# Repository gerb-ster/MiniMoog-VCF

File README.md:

# YUSynth MiniMoog VCF

No system is complete without some good VCF’s. And one excellent source for some good VCF is designs is, offcourse, the website of Yven Usson, also known as YuSynth. And this VCF is no exception. It’s a clone of the famous VCF found in the MiniMoog. I’ve made an eurorack version.

## Status: Finished

- done: first schematic & board design
- done: breadboard and test
- done: design frontpanel
- done: order PCB and build prototype

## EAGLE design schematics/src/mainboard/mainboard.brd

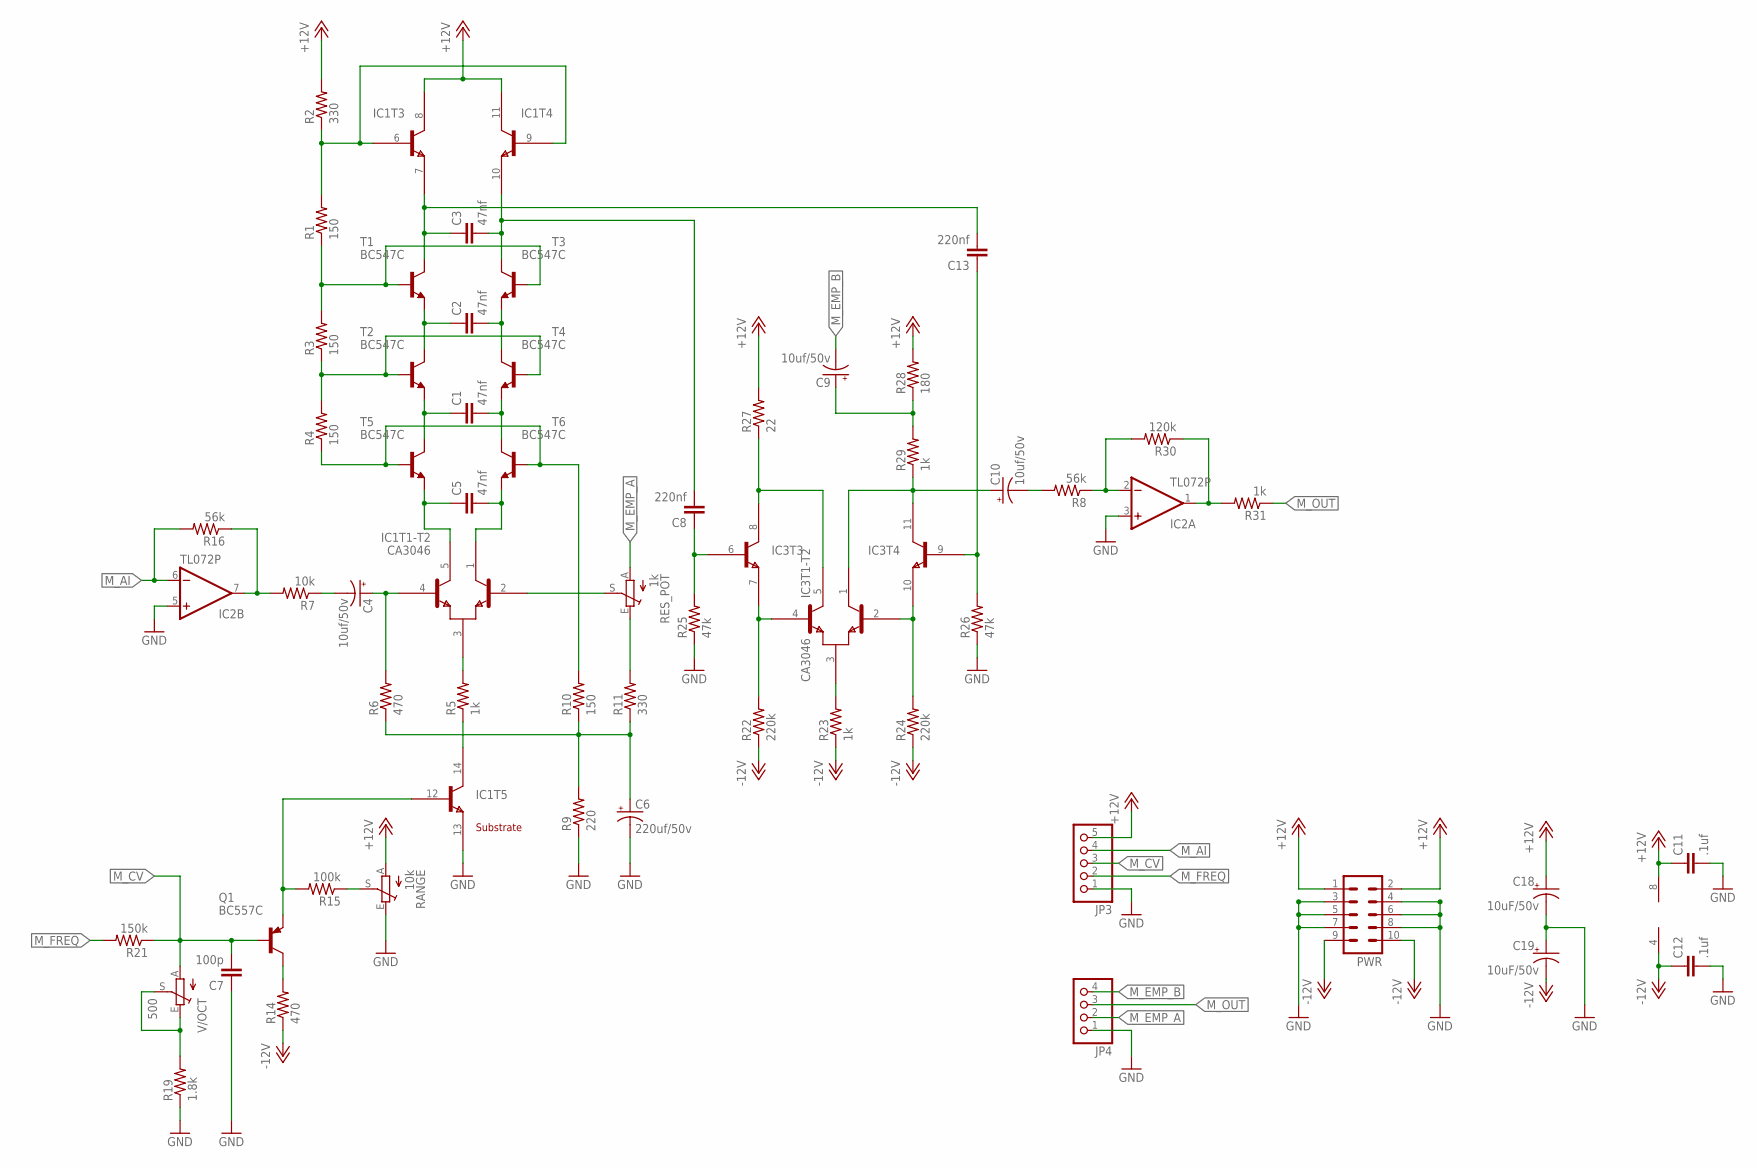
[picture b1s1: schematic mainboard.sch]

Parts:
C1, C2, C3, C5: 47nf; C050-024X044
C4, C9, C10: 10uf/50v; E2,5-5
C6: 220uf/50v; E3,5-10
C7: 100p; C050-024X044
C8, C13: 220nf; C050-024X044
C11, C12: .1uf; C050-024X044
C18, C19: 10uF/50v; E2,5-6
IC1, IC3: CA3046; DIL14
IC2: TL072P; DIL08
JP3: PINHD-1X5; 1X05
JP4: PINHD-1X4; 1X04
PWR: ML10
Q1: BC557C; TO92-EBC
R1, R3, R4, R10: 150; 0204/7
R2, R11: 330; 0204/7
R5, R23, R29, R31: 1k; 0204/7
R6, R14: 470; 0204/7
R7: 10k; 0204/7
R8, R16: 56k; 0204/7
R9: 220; 0204/7
R15: 100k; 0204/7
R19: 1.8k; 0204/7
R21: 150k; 0204/7
R22, R24: 220k; 0204/7
R25, R26: 47k; 0204/7
R27: 22; 0204/7
R28: 180; 0204/7
R30: 120k; 0204/7
RANGE: 10k; CA9V
RES_POT: 1k; CA9V
T1, T2, T3, T4, T5, T6: BC547C; TO92-CBE
V/OCT: 500; S64YW

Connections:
+12V: C11.1, C18.+, IC1.8 (C), IC1.11 (C), IC2.8 (V+), JP3.5, PWR.1, PWR.2, R2.2, R27.2, R28.2, RANGE.A
-12V: C12.1, C19.-, IC2.4 (V-), PWR.9, PWR.10, R14.1, R22.1, R23.1, R24.1
GND: C6.-, C7.1, C11.2, C12.2, C18.-, C19.+, IC1.13 (E), IC2.3 (+IN), IC2.5 (+IN), JP3.1, JP4.1, PWR.3, PWR.4, PWR.5, PWR.6, PWR.7, PWR.8, R9.1, R19.1, R25.1, R26.1, RANGE.E
M_AI: IC2.6 (-IN), JP3.4, R16.2
M_CV: C7.2, JP3.3, Q1.B, R21.1, V/OCT.A
M_EMP_A: JP4.2, RES_POT.A
M_EMP_B: C9.-, JP4.4
M_FREQ: JP3.2, R21.2
M_OUT: JP4.3, R31.1
unnamed: C5.1, IC1.5 (C2), T5.E
unnamed: IC1.6 (B), IC1.9 (B), R1.2, R2.1
unnamed: C3.1, C13.2, IC1.7 (E), T1.C
unnamed: C3.2, C8.2, IC1.10 (E), T3.C
unnamed: C2.1, T1.E, T2.C
unnamed: C2.2, T3.E, T4.C
unnamed: C1.1, T2.E, T5.C
unnamed: C1.2, T4.E, T6.C
unnamed: R1.1, R3.2, T1.B, T3.B
unnamed: R3.1, R4.2, T2.B, T4.B
unnamed: R4.1, R10.2, T5.B, T6.B
unnamed: C5.2, IC1.1 (C1), T6.E
unnamed: IC1.3 (E), R5.2
unnamed: IC1.14 (C), R5.1
unnamed: C4.+, IC1.4 (B2), R6.2
unnamed: C4.-, R7.1
unnamed: C6.+, R6.1, R9.2, R10.1, R11.1
unnamed: IC2.7 (OUT), R7.2, R16.1
unnamed: R19.2, V/OCT.E, V/OCT.S
unnamed: IC1.12 (B), Q1.E, R15.2
unnamed: IC1.2 (B1), RES_POT.S
unnamed: R11.2, RES_POT.E
unnamed: C13.1, IC3.9 (B), R26.2
unnamed: Q1.C, R14.2
unnamed: R15.1, RANGE.S
unnamed: C10.-, R8.2
unnamed: IC3.4 (B2), IC3.7 (E), R22.2
unnamed: IC3.3 (E), R23.2
unnamed: IC3.2 (B1), IC3.10 (E), R24.2
unnamed: IC3.5 (C2), IC3.8 (C), R27.1
unnamed: C10.+, IC3.1 (C1), IC3.11 (C), R29.1
unnamed: C9.+, R28.1, R29.2
unnamed: IC2.1 (OUT), R30.1, R31.2
unnamed: C8.1, IC3.6 (B), R25.2
unnamed: IC2.2 (-IN), R8.1, R30.2

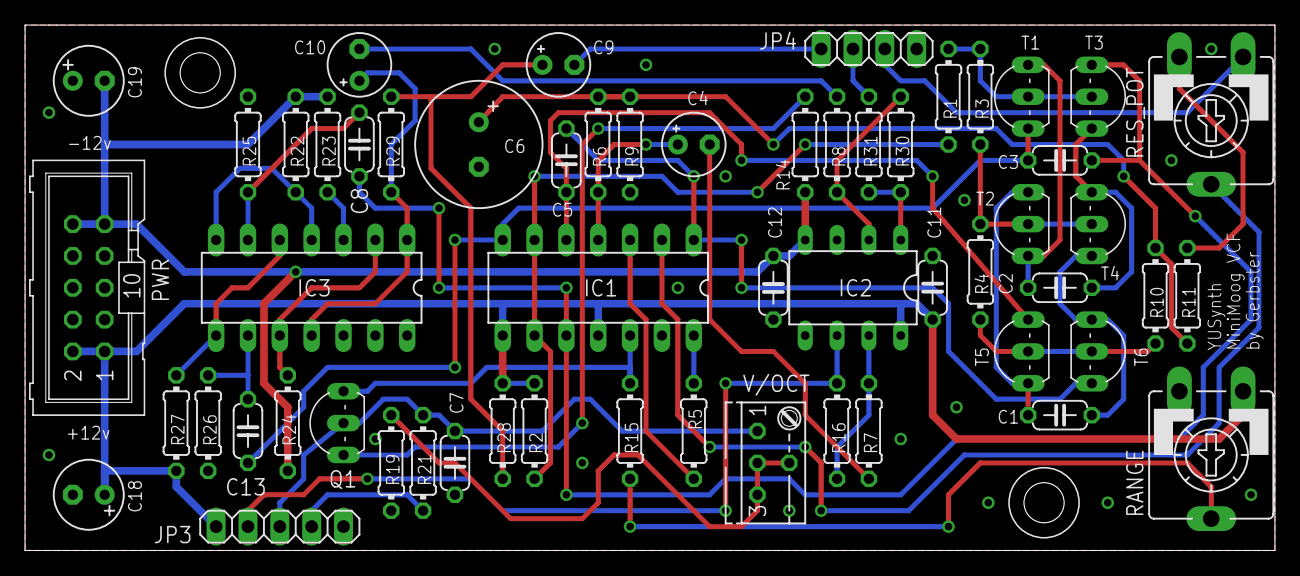
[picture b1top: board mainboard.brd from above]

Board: 2 copper layers, 99.7 x 41.9 mm, 57 parts (0 on the bottom side), 44 nets.

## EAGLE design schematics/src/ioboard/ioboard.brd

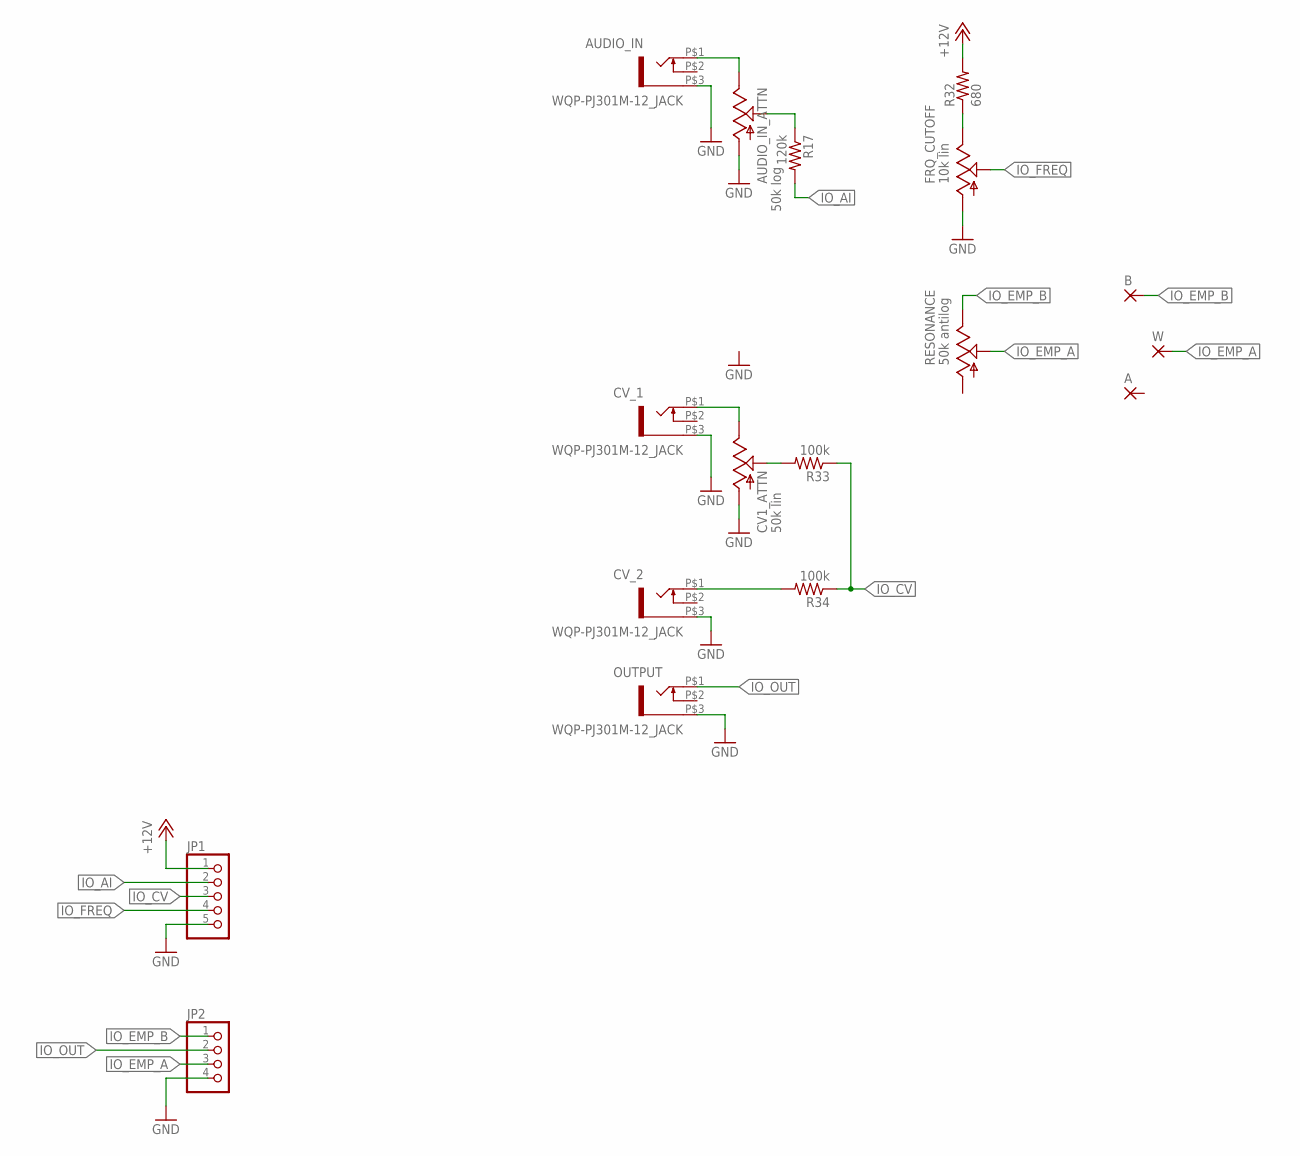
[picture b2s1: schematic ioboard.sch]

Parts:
A: 2,15/1,0
AUDIO_IN: WQP-PJ301M-12_JACK
AUDIO_IN_ATTN: 50k log; EVUF
B: 2,15/1,0
CV1_ATTN: 50k lin; EVUF
CV_1, CV_2: WQP-PJ301M-12_JACK
FRQ_CUTOFF: 10k lin; EVUF
JP1: PINHD-1X5; 1X05
JP2: PINHD-1X4; 1X04
OUTPUT: WQP-PJ301M-12_JACK
R17: 120k; 0204/7
R32: 680; 0204/7
R33, R34: 100k; 0204/7
RESONANCE: 50k antilog; EVUF
W: 2,15/1,0

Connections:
+12V: JP1.1, R32.2
GND: AUDIO_IN.P$3 (1), AUDIO_IN_ATTN.1 (A), CV1_ATTN.1 (A), CV_1.P$3 (1), CV_2.P$3 (1), FRQ_CUTOFF.1 (A), JP1.5, JP2.4, OUTPUT.P$3 (1)
IO_AI: JP1.2, R17.2
IO_AI_1: AUDIO_IN_ATTN.2 (S), R17.1
IO_CV: JP1.3, R33.1, R34.1
IO_EMP_A: JP2.3, RESONANCE.2 (S), W.1
IO_EMP_B: B.1, JP2.1, RESONANCE.3 (E)
IO_FREQ: FRQ_CUTOFF.2 (S), JP1.4
IO_OUT: JP2.2, OUTPUT.P$1 (2)
unnamed: FRQ_CUTOFF.3 (E), R32.1
unnamed: CV1_ATTN.3 (E), CV_1.P$1 (2)
unnamed: CV1_ATTN.2 (S), R33.2
unnamed: CV_2.P$1 (2), R34.2
unnamed: AUDIO_IN.P$1 (2), AUDIO_IN_ATTN.3 (E)

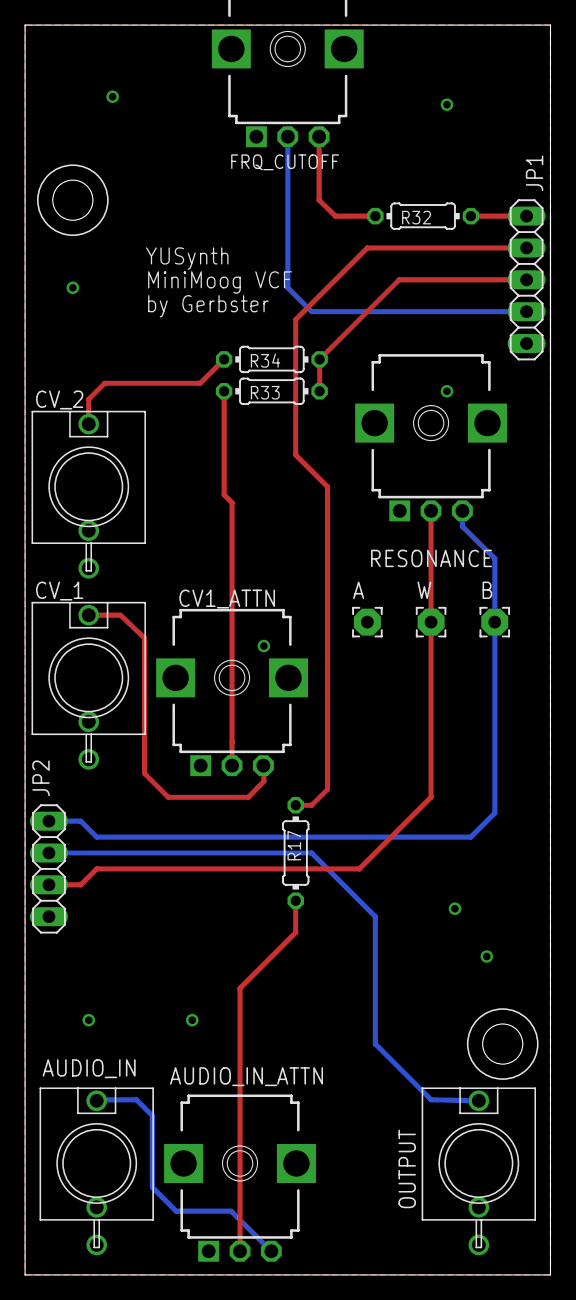
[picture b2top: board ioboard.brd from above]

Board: 2 copper layers, 41.9 x 99.7 mm, 17 parts (0 on the bottom side), 14 nets.

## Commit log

2021-05-06 some files
2021-05-07 Added files & structure
2021-05-10 Added Status
2021-05-11 Added Status & Images
2021-08-06 Updated some schematics and docs
2021-08-10 Fixed some bugs and updated documentation
2022-04-20 Some updates & bugfixes
2022-04-22 Fixed schematics & descriptions
2022-05-17 Updated Firmware
2022-05-18 Updated Faceplates
2022-05-18 Fixed issues
2022-05-21 Fixed schematics
2022-05-28 General updates
